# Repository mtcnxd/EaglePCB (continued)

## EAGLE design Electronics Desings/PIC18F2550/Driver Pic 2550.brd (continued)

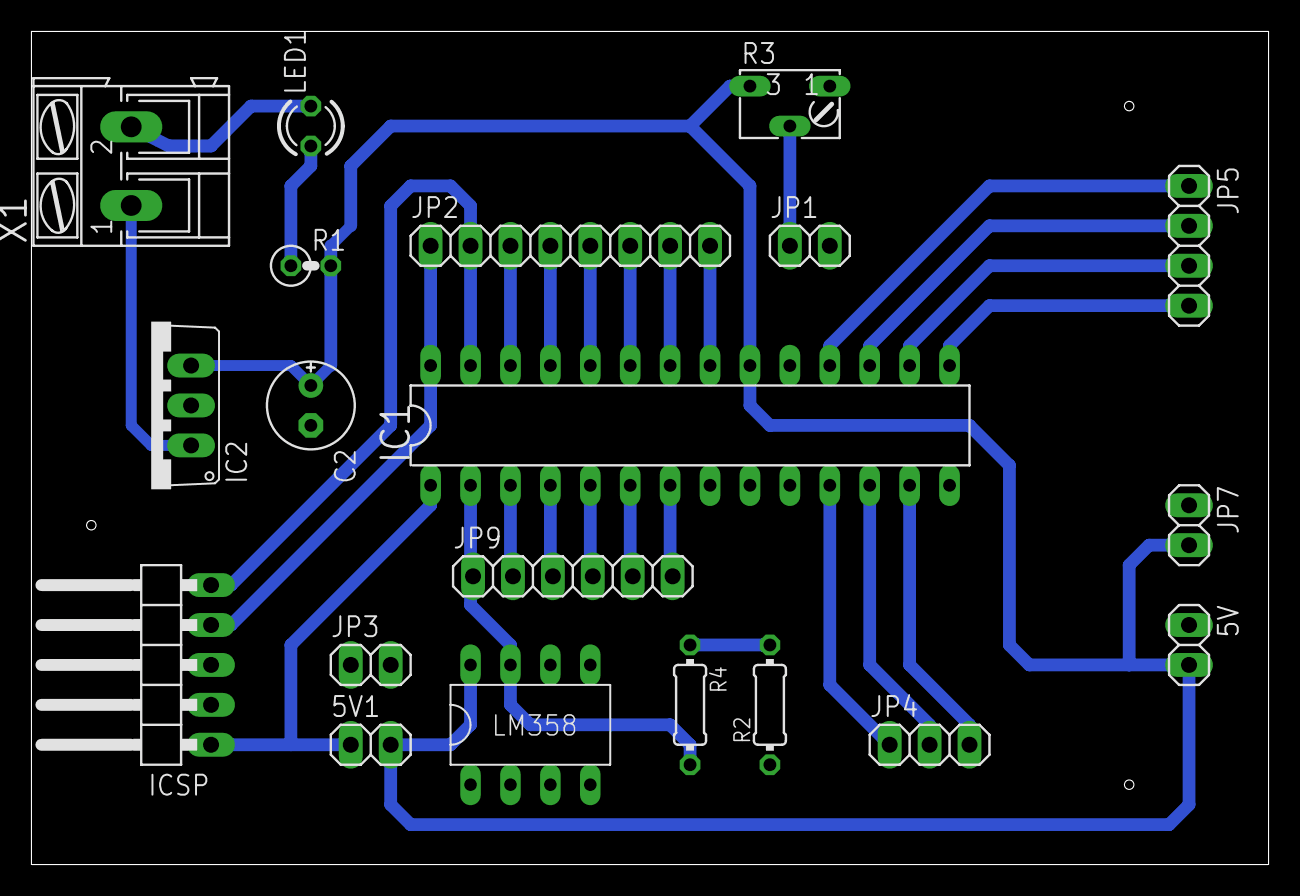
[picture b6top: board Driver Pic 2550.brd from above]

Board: 2 copper layers, 78.7 x 53.0 mm, 20 parts (0 on the bottom side), 29 nets.

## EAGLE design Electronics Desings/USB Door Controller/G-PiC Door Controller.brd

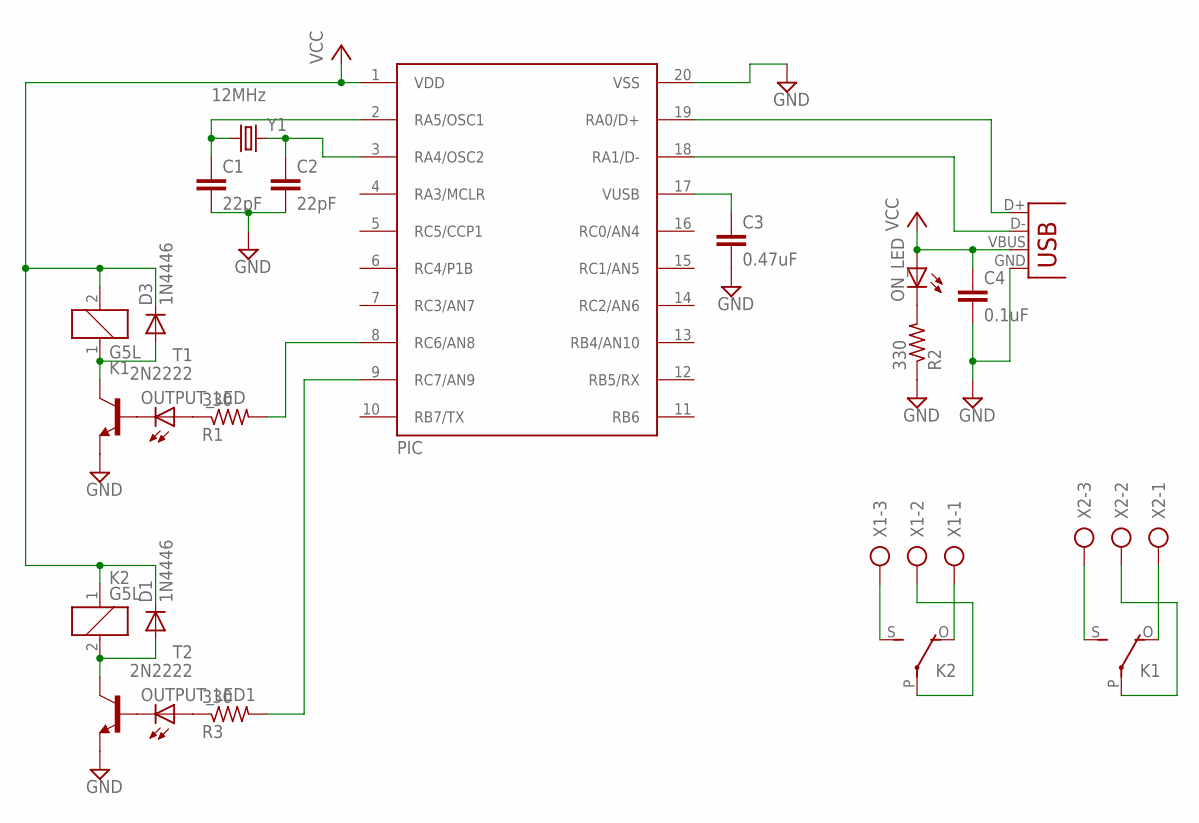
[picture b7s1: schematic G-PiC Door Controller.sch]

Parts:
C1, C2: 22pF; C5B3
C3: 0.47uF; C5B3
C4: 0.1uF; C2.5-3
D1, D3: 1N4446; DO35-10
K1, K2: G5L; G5LE
ON_LED: LED3MM
OUTPUT_LED, OUTPUT_LED1: LED3MM
PIC: PIC18F14K50; DIL20
R1, R2, R3: 330; 0204/7
T1, T2: 2N2222; TO92-EBC-OVAL
X1, X2: AK500/3-H
X3: USBPTH; USB-B-PTH
Y1: 12MHz; HC49US

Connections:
GND: C1.2, C2.2, C3.2, C4.2, PIC.20 (VSS), R2.1, T1.E, T2.E, X3.GND
unnamed: D3.A, K1.1, T1.C
unnamed: OUTPUT_LED.K (C), T1.B
unnamed: OUTPUT_LED.A, R1.1
unnamed: D1.A, K2.2, T2.C
unnamed: PIC.8 (RC6/AN8), R1.2
unnamed: ON_LED.K (C), R2.2
unnamed: C2.1, PIC.3 (RA4/OSC2), Y1.2
unnamed: C1.1, PIC.2 (RA5/OSC1), Y1.1
unnamed: OUTPUT_LED1.A, R3.1
unnamed: PIC.9 (RC7/AN9), R3.2
unnamed: C3.1, PIC.17 (VUSB)
unnamed: K1.O, X2.1
unnamed: K1.S, X2.3
unnamed: K1.P, X2.2
unnamed: PIC.19 (RA0/D+), X3.D+
unnamed: PIC.18 (RA1/D-), X3.D-
unnamed: OUTPUT_LED1.K (C), T2.B
unnamed: K2.S, X1.3
unnamed: K2.O, X1.1
unnamed: K2.P, X1.2
VCC: C4.1, D1.C, D3.C, K1.2, K2.1, ON_LED.A, PIC.1 (VDD), X3.VBUS

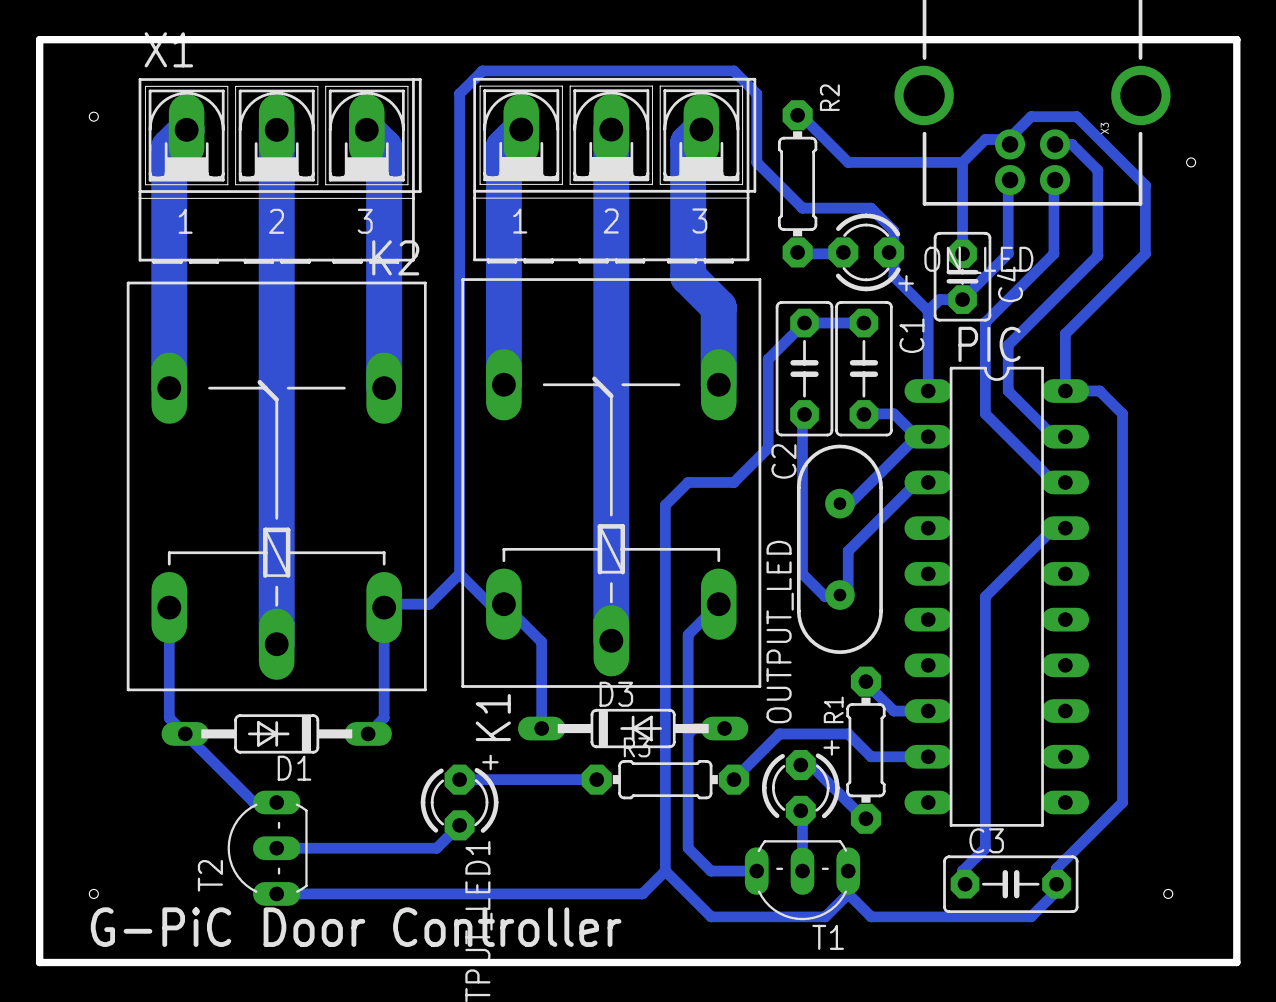
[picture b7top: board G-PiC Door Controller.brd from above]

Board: 2 copper layers, 66.5 x 51.3 mm, 21 parts (0 on the bottom side), 22 nets.
